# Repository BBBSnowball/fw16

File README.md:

see [here](https://community.frame.work/t/e-paper-module-to-replace-spacers-in-palm-rest/50784) until we add a proper README

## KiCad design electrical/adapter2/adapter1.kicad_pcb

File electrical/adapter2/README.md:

Framework Keypad uses only one of the USB slots,
so we can sneak in a flex PCB and extract USB for
a RP2040-tiny board in the lower half (i.e. left
or right of the touchpad module).

Parameters (JLCPCB)
----------

- Flex PCB, 2 layers
- PCB Thickness: 0.11 mm
- Coverlay Color: Yellow
- Gold: 1U
- Copper: 1/3 oz (12 um)
- Gold Fingers: yes, 0.3 mm
- Stiffener: Polyimide, 0.225 mm

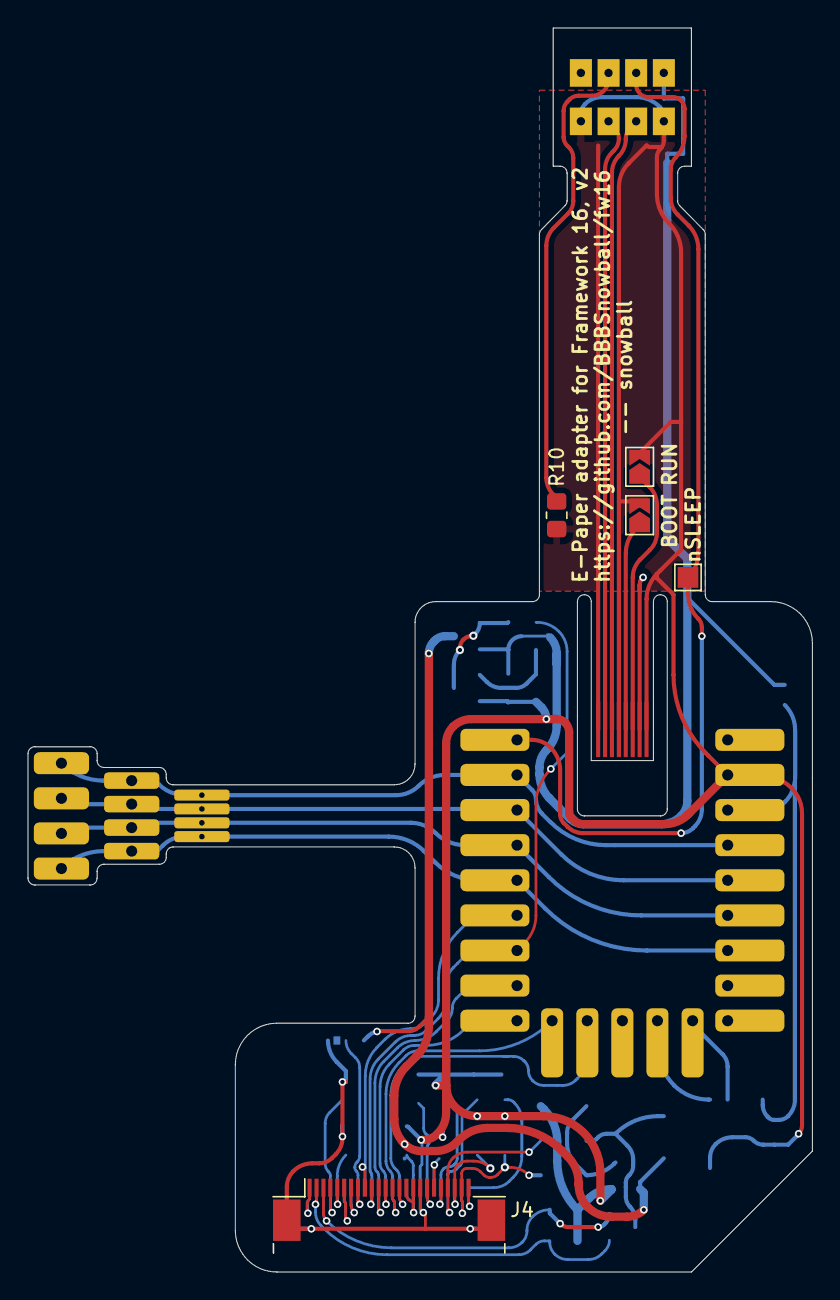
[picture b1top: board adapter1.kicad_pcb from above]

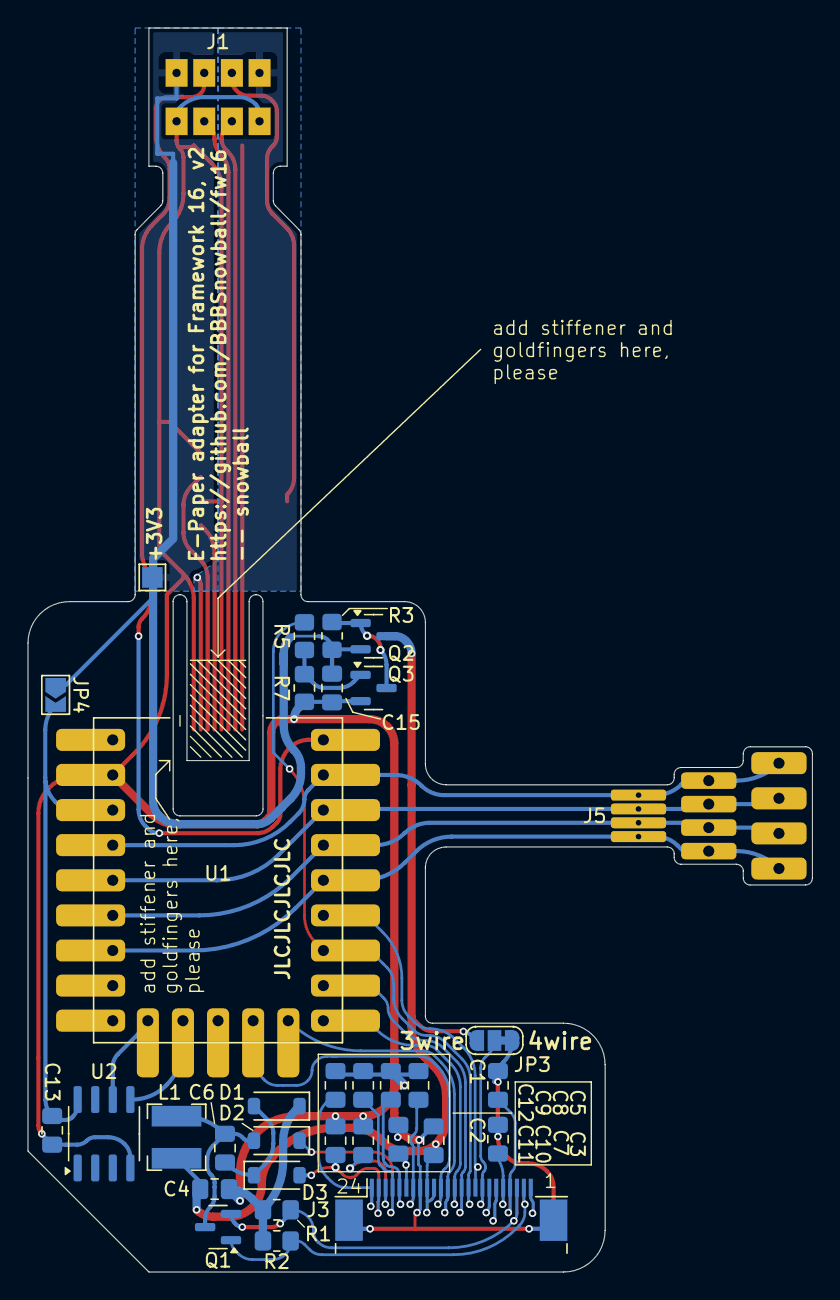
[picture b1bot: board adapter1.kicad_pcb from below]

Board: 2 copper layers, 56.8 x 90.0 mm, 40 parts (34 on the bottom side), 42 nets.

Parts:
C1, C2, C5, C7, C8, C9, C10, C11, C12: 105; C_0805_2012Metric_Pad1.18x1.45mm_HandSolder
C3, C15: 104 !; C_0805_2012Metric_Pad1.18x1.45mm_HandSolder
C4, C6: 4.7uF/50V; C_0805_2012Metric_Pad1.18x1.45mm_HandSolder
C13: 100n; C_0805_2012Metric_Pad1.18x1.45mm_HandSolder
D1, D2, D3: MBR0530; D_SOD-123
J1: PogoPads_2x4_P2.0mm_FPC
J2: Conn_01x08_Pin; GoldFingersRP2040Tiny
J3, J4: 0.5 mm, 24P; Jushuo_AFC07-S24FCA-00_1x24-1MP_P0.50_Horizontal
J5: TouchConnector
JP1, JP2, JP4: SolderJumper_2_Open; SolderJumper-2_P1.3mm_Open_TrianglePad1.0x1.5mm
JP3: SolderJumper_3_Bridged12; SolderJumper-3_P1.3mm_Bridged12_RoundedPad1.0x1.5mm
L1: 68uH; L_Bourns-SRN4018
Q1: BSS138; SOT-23
Q2: AO3401A; SOT-23
Q3: S8050 SMD; SOT-23
R1: 0.47R; R_0805_2012Metric_Pad1.20x1.40mm_HandSolder
R2, R5: 10k; R_0805_2012Metric_Pad1.20x1.40mm_HandSolder
R3: 100k; R_0805_2012Metric_Pad1.20x1.40mm_HandSolder
R7: 47k; R_0805_2012Metric_Pad1.20x1.40mm_HandSolder
R10: DNP; R_0805_2012Metric_Pad1.20x1.40mm_HandSolder
TP1, TP2: TestPoint; TestPoint_Pad_1.5x1.5mm
U1: RP2040-Tiny
U2: ATECC608B-SSHDA; SOIC-8_3.9x4.9mm_P1.27mm

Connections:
+3V3: C15.2, J1.8 (+3V3), JP4.1 (A), Q2.2 (S), R3.2, TP2.1
+5V: J1.2 (+5V), J2.7
/3V3_EP: C3.2, C4.2, J3.9, J3.10, J4.15, J4.16, JP3.3 (B), L1.1, Q2.3 (D)
/3V3_RPI: C13.2, JP4.2 (B), U1.20 (3V3), U2.8 (VCC)
/BOOT: J2.5, JP2.1 (A)
/BS: J3.17, J4.8, JP3.2 (C)
/BUSY: J3.16, J4.9, U1.5
/CS: J3.13, J4.12, U1.8
/DC: J3.14, J4.11, U1.7
/DIN: J3.11, J4.14, U1.10
/GDR: J3.23, J4.2, Q1.1 (G), R2.2
/PREVGH: C9.2, D3.1 (K), J3.4, J4.21
/PREVGL: C11.2, D2.2 (A), J3.2, J4.23
/RESE: J3.22, J4.3, Q1.2 (S), R1.2
/RST: J3.15, J4.10, R5.2, U1.6
/RUN: J2.6, JP1.1 (A)
/SCK: J3.12, J4.13, U1.9
/SCL: U1.13, U2.6 (SCL)
/SDA: U1.12, U2.5 (SDA)
/SLEEP: J1.6 (nSLEEP), TP1.1, U1.0
/USB_N: J1.3 (USB_DN), J2.2
/USB_P: J1.5 (USB_DP), J2.3
GND: C1.1, C2.1, C3.1, C4.1, C5.1, C7.1, C8.1, C9.1, C10.1, C11.1, C12.1, C13.1, C15.1, D1.1 (K), J1.1 (GND), J1.7 (GND), J2.1, J2.4, J2.8, J3.8, J3.MP (MountPin), J4.17, J4.MP (MountPin), JP1.2 (B), JP2.2 (B), JP3.1 (A), Q3.2 (E), R1.1, R2.1, R7.1, R10.2, U1.21 (GND), U2.4 (GND)
unnamed: C6.1, D1.2 (A), D2.1 (K)
unnamed: C6.2, D3.2 (A), L1.2, Q1.3 (D)
unnamed: J1.4 (BOARD_ID), R10.1
unnamed: C12.2, J3.1, J4.24
unnamed: C10.2, J3.3, J4.22
unnamed: C8.2, J3.5, J4.20
unnamed: C7.2, J3.6, J4.19
unnamed: C5.2, J3.7, J4.18
unnamed: J3.18, J4.7
unnamed: J3.19, J4.6
unnamed: C2.2, J3.20, J4.5
unnamed: C1.2, J3.21, J4.4
unnamed: J3.24, J4.1
unnamed: J5.1, U1.1, U1.19 (29)
unnamed: J5.2, U1.2, U1.18 (28)
unnamed: J5.3, U1.3, U1.17 (27)
unnamed: J5.4, U1.4, U1.16 (26)
unnamed: Q2.1 (G), Q3.3 (C), R3.1
unnamed: Q3.1 (B), R5.1, R7.2

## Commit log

2024-03-30 initial commit: new PlatformIO project
2024-03-30 add WaveShare example code
    from https://files.waveshare.com/upload/7/71/E-Paper_code.zip,
    directory Arduino/epd4in01f
2024-03-30 adjust pinout and SPI implementation
2024-03-30 refactoring
2024-03-30 try partial refresh -> doesn't work
2024-03-31 use lambda for image data
2024-03-31 implement partial mode
2024-03-31 implement partial RAM updates
2024-03-31 refactoring: make EdpUpdate class to remove redundant code
2024-03-31 implement simple protocol over USB serial
2024-03-31 add example image and Python script
2024-03-31 do scaling and dithering with Python
    There is no need to do this in Gimp because we are using the
    pillow library anyway, which can do this just fine.
2024-04-03 fixup: add missing file
2024-04-03 fixup: don't ignore color argument for Clear
2024-04-03 add more example images
2024-04-03 use more realistic palette
2024-04-12 add first version of FPC adapter
2024-04-12 fix warnings
2024-04-12 add README and gerbers for "adapter1"
2024-04-12 add silk text for stiffener
2024-04-13 add VS Code file
2024-04-13 make copy of firmware project
2024-04-13 add more Waveshare example code
    from https://files.waveshare.com/upload/7/71/E-Paper_code.zip,
    directory Arduino/epd3in7
2024-04-13 adjust files for RP2040
2024-04-14 copy PCB
2024-04-14 start working on adapter2 PCB
2024-04-14 adapter2: routing done and DRC clean
2024-04-14 final (?) touches
2024-04-14 fixup
2024-04-14 update gerbers
2024-04-14 remove hard corners from tracks
2024-04-14 fixup: silk line too thin
2024-04-14 add picture
2024-04-14 add link and description, adjust zones a bit
2024-04-14 add ATECC608
2024-04-16 add LCSC part numbers
2024-04-18 improve pad (solder mask) to copper clearance
    JLC say that it should be at least 0.25 mm.
2024-05-04 try and use ePaper interface on "adapter2" with SoftSPI -> doesn't work
2024-05-04 add simple test for ATECC608 security chip
2024-05-07 add FreeCAD file
2024-05-07 add test program for touch screen
2024-05-08 make Framework module 3D design for larger epaper
2024-05-10 fixup: it tried to use the wrong Arduino core
    see https://github.com/earlephilhower/arduino-pico/blob/master/docs/platformio.rst#current-state-of-development
2024-05-10 make it easier to disable our panic handler and add script with necessary patches
2024-05-10 add simple serial protocol
2024-05-11 send b&w image via USB
2024-05-11 add grayscale
2024-05-15 add test image
2024-05-16 add first code for APDS-9960 gesture sensor
2024-05-16 try gesture sensor for gestures -> not so great, yet
2024-05-16 add stub README
2024-05-16 adjust epaper cover
    - adjust cutout to better match active area of display
    - make some parts a bit thicker
2024-05-16 fixup: cutout for display still wasn't right
2024-05-16 update 3D model
